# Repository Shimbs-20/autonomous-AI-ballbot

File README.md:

# 🤖 Hazard Detection Ball Bot — Cairo University GP 2026

<div align="center">

**A self-balancing omnidirectional robot on a spherical wheel with real-time hazard detection, autonomous SLAM navigation, and a live web dashboard.**

*Cairo University · Faculty of Engineering · Mechatronics Graduation Project · Spring 2026*

</div>

---

## 📋 Table of Contents

- [Overview](#overview)
- [Demo](#demo)
- [Team](#team)
- [System Architecture](#system-architecture)
- [Hardware](#hardware)
- [Software Stack](#software-stack)
- [Repository Structure](#repository-structure)
- [Quick Start](#quick-start)
- [Control System](#control-system)
- [Navigation](#navigation)
- [Hazard Detection](#hazard-detection)
- [Web Dashboard](#web-dashboard)
- [Results](#results)
- [Bill of Materials](#bill-of-materials)
- [Acknowledgements](#acknowledgements)

---

## Overview

The Hazard Detection Ball Bot is an inverted-pendulum robot that balances on a single 350mm sphere driven by three omnidirectional wheels. It combines:

- **Real-time dynamic balancing** using a custom EKF (8-state) and LQI controller running at 200 Hz on STM32F411
- **Autonomous SLAM mapping** using a 360° LiDAR and slam_toolbox on Raspberry Pi 4
- **Hazard detection** using a custom-trained YOLOv8 NCNN model (fire, smoke, electrical hazard, person, obstacle) at 33+ FPS
- **Full ROS2 Navigation Stack** with MPPI holonomic controller for autonomous goal-seeking
- **Live web dashboard** accessible from any browser on the local network

The robot operates in four modes:
| Mode | Description |
|------|-------------|
| `0 STANDBY` | Motors off, safe state |
| `1 BALANCE` | Stationary self-balancing (LQI active) |
| `2 TELEOP` | Balance + velocity commands from Pi |
| `3 FLOOR DRIVE` | Direct omni-drive on casters (for SLAM mapping without balance risk) |

---

## Demo

> 📹 **[Demo Video — YouTube](#)** ← add link after recording

| SLAM Mapping | Hazard Detection | Dashboard |
|:---:|:---:|:---:|
|  |  |  |

---

## System Architecture

```
┌─────────────────────────────────────────────────────────────────────┐
│                        RASPBERRY PI 4B                              │
│                                                                     │
│  LD06 LiDAR ──→ /scan ──→ slam_toolbox ──→ /map                    │
│                              ↑                                      │
│  /odom ←── stm32_bridge ←── UART2 ←─────────────────────┐         │
│               │                                           │         │
│               └──→ twist_mux ──→ /cmd_vel ───────────────┘         │
│                      ↑              ↑                               │
│               PS4 joystick    Nav2 MPPI                             │
│                                                                     │
│  IMX219 ──→ /image_raw ──→ YOLOv8 NCNN ──→ /hazard_detections     │
│                                 └──→ /image_annotated               │
│                                                                     │
│  web_video_server (port 8080) + rosbridge (port 9090)               │
└──────────────────────────────┬──────────────────────────────────────┘
                               │ UART2 / 115200 baud
                               │ TX: 16-byte [AA][55][mode][vx][vy][yaw][XOR]
                               │ RX: 27-byte [BB][66][x][y][θ][vx][vy][yaw][XOR]
┌──────────────────────────────┴──────────────────────────────────────┐
│                    STM32F411 @ 96 MHz / FreeRTOS                    │
│                                                                     │
│  MPU6050 ──→ EKF (200 Hz, 8-state) ──→ LQI K[3×10]               │
│                        ↑                     ↓                      │
│  Encoders (TIM2/3/4) ──┘           convert_torque_to_speed          │
│                                             ↓                       │
│  TIM11 ISR (70021 Hz) ─── Bresenham ──→ 3× DM860H ──→ NEMA34      │
└─────────────────────────────────────────────────────────────────────┘
```

---

## Hardware

### Key Specifications

| Component | Specification |
|-----------|--------------|
| **Compute (embedded)** | STM32F411CEU6 @ 96 MHz, 128KB RAM |
| **Compute (high-level)** | Raspberry Pi 4B, 4GB RAM |
| **Motors** | 3× NEMA34 86BYGH127, 8.5 N·m holding torque |
| **Motor Drivers** | 3× DM860H, 48V / 7.2A, 16-microstep |
| **IMU** | MPU6050, ±16g / ±2000°/s, DLPF 44 Hz |
| **LiDAR** | LD06, 360°, 12m range, 230,400 baud |
| **Camera** | IMX219 (Pi Camera v2), 1080p, 30 FPS |
| **Ball** | 350mm diameter, rubber-tape coated, µ≈0.50 |
| **Battery** | 48V / 11Ah NMC (EV Raid) |
| **Total Height** | 925 mm |
| **Total Mass** | ~17 kg |

### Kinematic Geometry

```
Wheel placement:  γ₁=120°, γ₂=240°, γ₃=0° (equal spacing)
Zenith angle:     α = 45°
Ball radius:      Rk = 0.175 m
Wheel radius:     Rw = 0.0625 m
```

---

## Software Stack

```
Firmware (STM32):          ROS2 (Raspberry Pi):
  FreeRTOS                   ROS2 Humble / Jazzy
  STM32 HAL                  slam_toolbox (async SLAM)
  EKF (custom C)             Nav2 (MPPI Omni)
  LQI controller             AMCL localization
  USART2 DMA                 twist_mux
  Bresenham step engine      web_video_server
                             rosbridge_websocket
Vision:                    Dashboard:
  OpenCV                     HTML5 / JavaScript
  Ultralytics YOLOv8         ROSLIB.js
  NCNN inference             Web Video Server MJPEG
```

---

## Repository Structure

```
ballbot/
├── README.md
├── LICENSE
├── .gitignore
│
├── firmware/                   STM32CubeIDE project
│   ├── Core/
│   │   ├── Src/
│   │   │   ├── main.c          Main control loop (Modes 0-3)
│   │   │   ├── lqr.c           LQI controller + EKF interface
│   │   │   ├── Ekf.c           Extended Kalman Filter (8-state)
│   │   │   └── mpu6050.c       IMU driver
│   │   └── Inc/
│   │       ├── lqr.h
│   │       └── Ekf.h
│   └── README.md
│
├── ros2_ws/                    ROS2 workspace
│   └── src/
│       ├── ballbot_controller/ Bridge, teleop, mode control
│       ├── ballbot_mapping/    SLAM toolbox config + launch
│       ├── ballbot_navigation/ Nav2 params, behavior tree
│       ├── camera_pi/          Camera node + YOLOv8 detector
│       └── gp_description/     URDF + mesh files
│
├── matlab/                     Design and simulation
│   ├── system_model/           Nonlinear ball-bot dynamics
│   ├── lqi_design/             LQI gain matrix K[3×10] derivation
│   ├── ekf_design/             EKF Q/R tuning + verification
│   └── simulation/             Full closed-loop Simulink model
│
├── hardware/
│   ├── cad/                    SolidWorks assembly (.SLDASM, .STEP)
│   ├── pcb/                    Custom power board schematics
│   ├── BOM.md                  Complete bill of materials
│   └── README.md
│
└── dashboard/
    └── dashboard.html          Standalone web dashboard
```

---

## Quick Start

### Prerequisites

```bash
# On Raspberry Pi 4B — Bookworm 64-bit
sudo apt install -y ros-humble-desktop python3-colcon-common-extensions \
    ros-humble-slam-toolbox ros-humble-nav2-bringup \
    ros-humble-rosbridge-server ros-humble-web-video-server

pip install ultralytics opencv-python picamera2
```

### Build

```bash
cd ~/ros2_ws
colcon build --symlink-install
source install/setup.bash
```

### Run — Hardware bringup (Terminal 1)

```bash
# Testing without STM32
ros2 launch ballbot_controller pi_controller.launch.py

# Real robot — stationary balance
ros2 launch ballbot_controller pi_controller.launch.py \
    use_fake_odom:=false robot_mode:=1

# Real robot — SLAM mapping on floor (safest)
ros2 launch ballbot_controller pi_controller.launch.py \
    use_fake_odom:=false robot_mode:=3
```

### Run — SLAM mapping (Terminal 2)

```bash
ros2 launch ballbot_mapping slam.launch.py use_slam:=true

# Drive to map:
ros2 run teleop_twist_keyboard teleop_twist_keyboard

# Save when done:
ros2 run nav2_map_server map_saver_cli -f ~/maps/room
```

### Run — Autonomous navigation (Terminal 2)

```bash
ros2 launch ballbot_mapping slam.launch.py \
    use_slam:=false map_yaml:=~/maps/room.yaml

ros2 launch ballbot_navigation nav2.launch.py \
    use_slam:=false shelf_test:=false
# Then: RViz → 2D Pose Estimate → 2D Nav Goal
```

### Run — Camera + Hazard detection (Terminal 3)

```bash
ros2 launch camera_pi hazard.launch.py
# Dashboard: http://ballbot.local:8080
```

### Switch robot modes at runtime

```bash
ros2 topic pub --once /ballbot/mode std_msgs/msg/UInt8 '{data: 1}'  # BALANCE
ros2 topic pub --once /ballbot/mode std_msgs/msg/UInt8 '{data: 2}'  # TELEOP
ros2 topic pub --once /ballbot/mode std_msgs/msg/UInt8 '{data: 3}'  # FLOOR DRIVE
```

---

## Control System

### EKF — 8-State Observer

State vector: `[φ, θ, dφ, dθ, Vx, Vy, bias_x, bias_y]`

- **Sensor fusion**: MPU6050 gyro + accelerometer + 3 wheel encoders
- **Accelerometer spike rejection**: rejects readings outside [0.2g, 15g]
- **Motor-aware noise**: R_accel scales with motor speed (30→250)
- **Execution time**: ~0.4ms @96MHz (Joseph-form covariance update)

### LQI Controller — K[3×10]

```
Torque = −K × [φ, θ, ψ, Vx, Vy, dφ, dθ, ω_z, ∫Vx, ∫Vy]ᵀ
```

Gains tuned in MATLAB for: m=17kg, Rk=0.175m, Rw=0.0625m, α=45°, J_wheel=0.0032 kg·m²

### Inverse Kinematics (Mode 3 — Floor Drive)

Pseudo-inverse of forward kinematic matrix (verified: K·K⁺=I₂ₓ₂):

```
ω₁ = −1.617·vx − 0.933·vy + 1.980·ω_z
ω₂ = +1.617·vx − 0.933·vy + 1.980·ω_z
ω₃ = +0.000·vx + 1.867·vy + 1.980·ω_z
```

---

## Navigation

- **SLAM**: slam_toolbox async_online, 5cm/cell, Ceres solver
- **Localization**: AMCL with OmniMotionModel
- **Planner**: SmacPlanner2D (A*, holonomic — no heading constraint)
- **Controller**: MPPI, 300 trajectories, `motion_model: Omni`, vy_max=0.5 m/s
- **Behavior tree**: ClearCostmap → Spin → BackUp → Wait
- **Velocity arbitration**: twist_mux — PS4(100) > keyboard(50) > Nav2(10)

---

## Hazard Detection

| Class | mAP@0.5 | Triggers E-Stop |
|-------|---------|-----------------|
| 🔥 Fire | 94.2% | ✅ |
| 💨 Smoke | 91.8% | ✅ |
| ⚡ Electrical Hazard | 88.7% | ✅ |
| 👤 Person | 96.5% | ❌ |
| 🚧 Obstacle | 85.3% | ❌ |

- **Model**: YOLOv8n converted to NCNN for Pi 4 CPU inference
- **Input**: 416×416 letterbox (aspect-ratio preserving)
- **Output**: 640×480 annotated MJPEG to web dashboard
- **Throughput**: 33.4 FPS average on Raspberry Pi 4B

---

## Web Dashboard

Accessible at `http://ballbot.local:8080` or `http://<Pi-IP>:8080`

**Features:**
- Live MJPEG camera feed (annotated with bounding boxes)
- Real-time SLAM map rendering from `/map` OccupancyGrid
- LiDAR scan overlay on map
- Odometry trail
- Mode control buttons (0/1/2/3) via `/ballbot/mode`
- Hazard detection cards with proximity indicator
- CPU temperature gauge
- Emergency stop overlay

**Dependencies:** rosbridge_websocket (port 9090), web_video_server (port 8080)

---

## Results

| Metric | Value |
|--------|-------|
| Control loop frequency | 200 Hz |
| EKF execution time | ~0.4 ms |
| Stepper ISR frequency | 70,021 Hz |
| SLAM map resolution | 5 cm/cell |
| Nav2 goal success rate | 100% (lab trials) |
| Detection FPS | 33.4 FPS |
| Detection classes | 5 |
| Total system mass | 17 kg |
| Battery endurance | ~2 hours |

---

## Bill of Materials

See [`hardware/BOM.md`](hardware/BOM.md) for the complete list.

**Major components:**

| Item | Qty | Est. Cost |
|------|-----|-----------|
| STM32F411 Black Pill | 1 | $5 |
| Raspberry Pi 4B 4GB | 1 | $55 |
| NEMA34 stepper 86BYGH127 | 3 | $45 each |
| DM860H stepper driver | 3 | $30 each |
| MPU6050 IMU module | 1 | $3 |
| LD06 LiDAR | 1 | $90 |
| Pi Camera Module v2 (IMX219) | 1 | $25 |
| 48V 11Ah NMC battery pack | 1 | $120 |
| Omni roller ball 350mm | 1 | $80 |
| **Total (approx.)** | | **~$1,480** |

---

## Acknowledgements

This project was completed as the Graduation Project 2 (GP2) for the Mechatronics program at Cairo University Faculty of Engineering, Spring 2026.

We thank Dr. Hossam H. Ammar and Dr. Moataz El-Sisi for their guidance throughout the project.

**References:**
- Lauwers, T. B. et al., "A Dynamically Stable Single-Wheeled Mobile Robot with Inverse Mouse-Ball Drive" — ICRA 2006
- Geyer, H., "Ballbot: The Fast, Omnidirectional Balancing Mobile Robot" — CMU 2010
- Welch, G. and Bishop, G., "An Introduction to the Kalman Filter" — UNC 1995

---

<div align="center">
Cairo University · Faculty of Engineering · Spring 2026
</div>

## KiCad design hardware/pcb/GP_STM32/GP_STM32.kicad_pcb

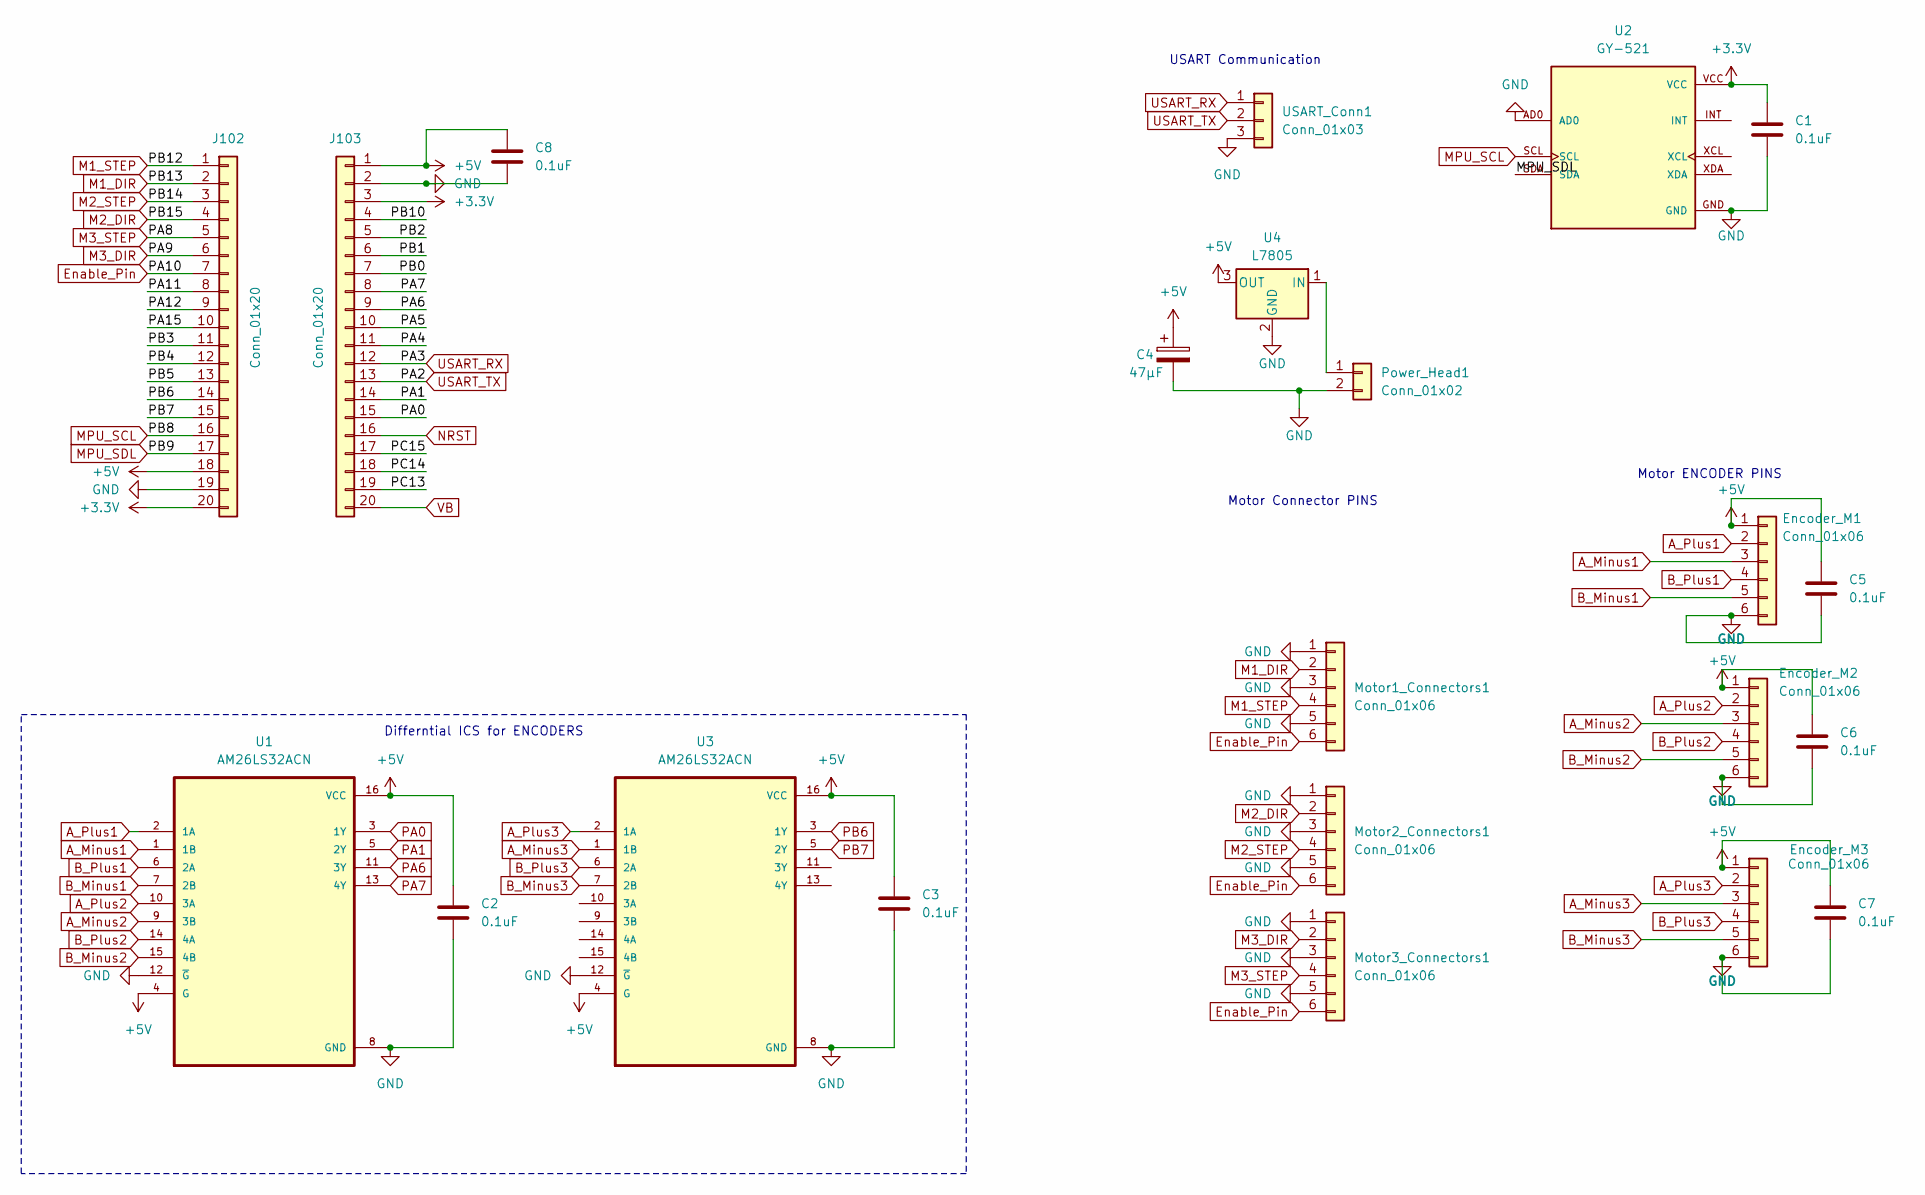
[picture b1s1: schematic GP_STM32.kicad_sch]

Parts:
C1, C2, C3, C5, C6, C7, C8: 0.1uF; C_Disc_D5.0mm_W2.5mm_P5.00mm
C4: 47µF; CP_Radial_D6.3mm_P2.50mm
Encoder_M1, Encoder_M2, Encoder_M3: Conn_01x06; JST_XH_B6B-XH-A_1x06_P2.50mm_Vertical
J102, J103: Conn_01x20; PinHeader_1x20_P2.54mm_Vertical
Motor1_Connectors1, Motor2_Connectors1, Motor3_Connectors1: Conn_01x06; JST_XH_B6B-XH-A_1x06_P2.50mm_Vertical
Power_Head1: Conn_01x02; TerminalBlock_MaiXu_MX126-5.0-02P_1x02_P5.00mm
U1, U3: AM26LS32ACN; DIP-16_W7.62mm
U2: GY-521; MODULE_GY-521; PARTREV NA
U4: L7805; TO-220-3_Vertical
USART_Conn1: Conn_01x03; JST_XH_B3B-XH-A_1x03_P2.50mm_Vertical

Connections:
+3.3V: C1.1, J102.20, J103.3, U2.VCC
+5V: C2.1, C3.1, C4.1, C5.1, C6.1, C7.1, C8.1, Encoder_M1.1, Encoder_M2.1, Encoder_M3.1, J102.18, J103.1, U1.4 (G), U1.16 (VCC), U3.4 (G), U3.16 (VCC), U4.3 (OUT)
/PA4: J103.11
/PA5: J103.10
/PA11: J102.8
/PA12: J102.9
/PA15: J102.10
/PB0: J103.7
/PB1: J103.6
/PB2: J103.5
/PB3: J102.11
/PB4: J102.12
/PB5: J102.13
/PB10: J103.4
/PC13: J103.19
/PC14: J103.18
/PC15: J103.17
A_Minus1: Encoder_M1.3, U1.1 (1B)
A_Minus2: Encoder_M2.3, U1.9 (3B)
A_Minus3: Encoder_M3.3, U3.1 (1B)
A_Plus1: Encoder_M1.2, U1.2 (1A)
A_Plus2: Encoder_M2.2, U1.10 (3A)
A_Plus3: Encoder_M3.2, U3.2 (1A)
B_Minus1: Encoder_M1.5, U1.7 (2B)
B_Minus2: Encoder_M2.5, U1.15 (4B)
B_Minus3: Encoder_M3.5, U3.7 (2B)
B_Plus1: Encoder_M1.4, U1.6 (2A)
B_Plus2: Encoder_M2.4, U1.14 (4A)
B_Plus3: Encoder_M3.4, U3.6 (2A)
Enable_Pin: J102.7, Motor1_Connectors1.6, Motor2_Connectors1.6, Motor3_Connectors1.6
GND: C1.2, C2.2, C3.2, C4.2, C5.2, C6.2, C7.2, C8.2, Encoder_M1.6, Encoder_M2.6, Encoder_M3.6, J102.19, J103.2, Motor1_Connectors1.1, Motor1_Connectors1.3, Motor1_Connectors1.5, Motor2_Connectors1.1, Motor2_Connectors1.3, Motor2_Connectors1.5, Motor3_Connectors1.1, Motor3_Connectors1.3, Motor3_Connectors1.5, Power_Head1.2, U1.8 (GND), U1.12 (~G), U2.AD0, U2.GND, U3.8 (GND), U3.12 (~G), U4.2 (GND), USART_Conn1.3
M1_DIR: J102.2, Motor1_Connectors1.2
M1_STEP: J102.1, Motor1_Connectors1.4
M2_DIR: J102.4, Motor2_Connectors1.2
M2_STEP: J102.3, Motor2_Connectors1.4
M3_DIR: J102.6, Motor3_Connectors1.2
M3_STEP: J102.5, Motor3_Connectors1.4
MPU_SCL: J102.16, U2.SCL
MPU_SDL: J102.17, U2.SDA
NRST: J103.16
unnamed: Power_Head1.1, U4.1 (IN)
PA0: J103.15, U1.3 (1Y)
PA1: J103.14, U1.5 (2Y)
PA6: J103.9, U1.11 (3Y)
PA7: J103.8, U1.13 (4Y)
PB6: J102.14, U3.3 (1Y)
PB7: J102.15, U3.5 (2Y)
USART_RX: J103.12, USART_Conn1.1
USART_TX: J103.13, USART_Conn1.2
VB: J103.20

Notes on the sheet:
Differntial ICS for ENCODERS
USART Communication
Motor Connector PINS
Motor ENCODER PINS

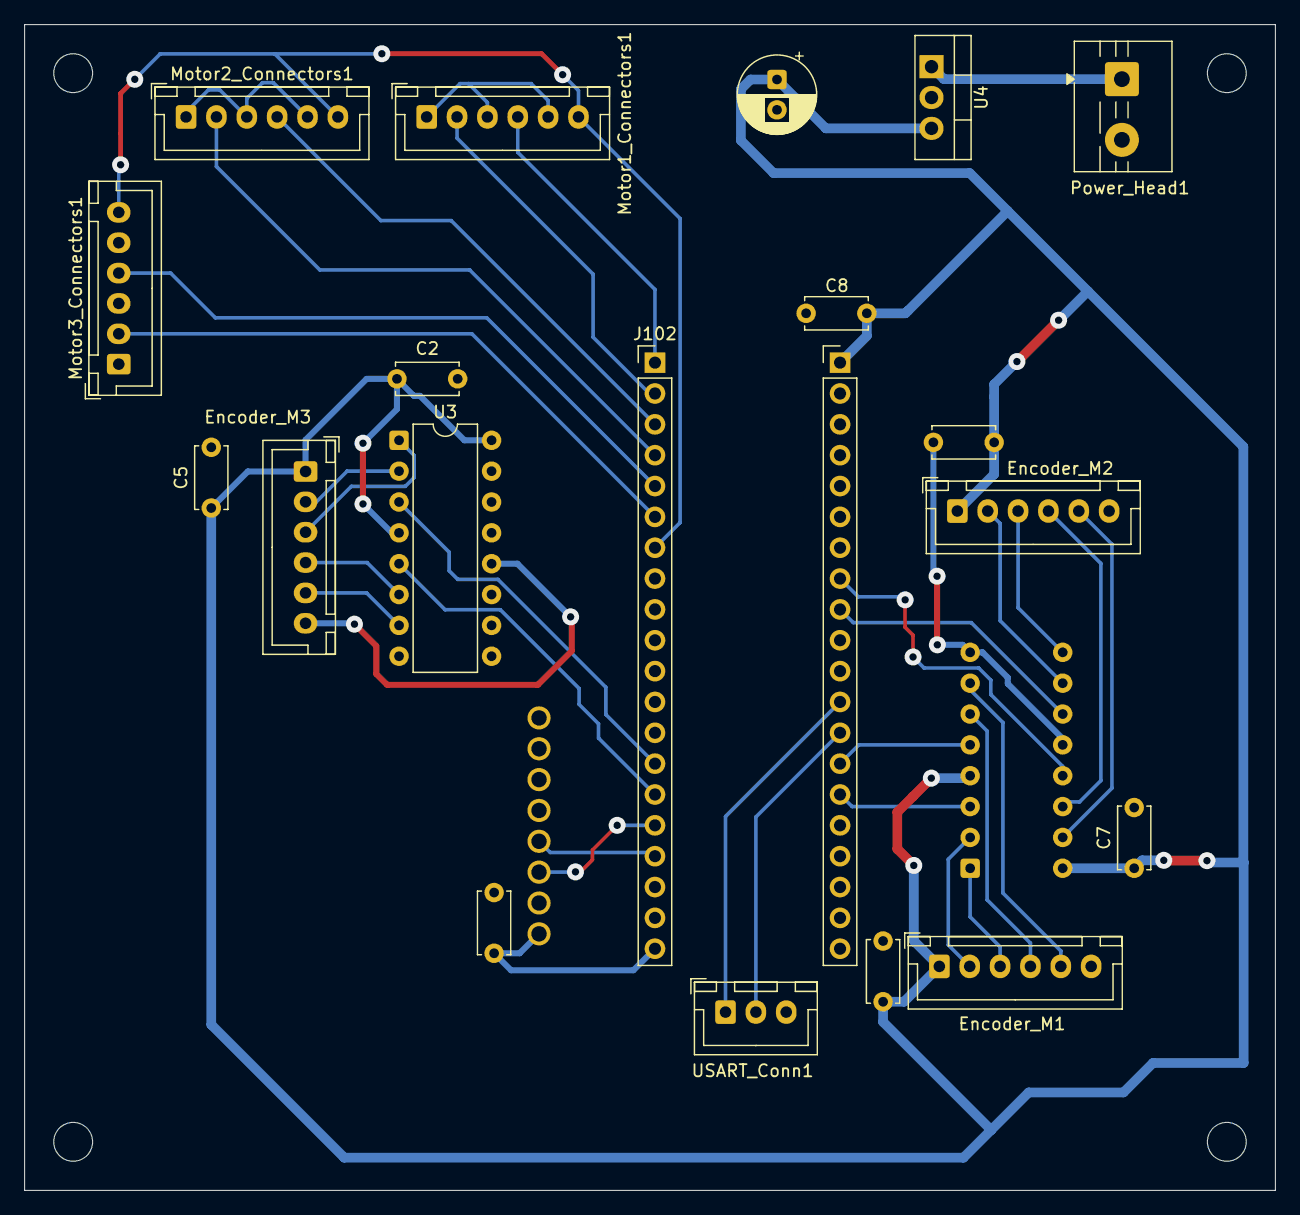
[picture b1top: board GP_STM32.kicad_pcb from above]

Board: 2 copper layers, 103.0 x 96.0 mm, 22 parts (1 on the bottom side), 33 nets.

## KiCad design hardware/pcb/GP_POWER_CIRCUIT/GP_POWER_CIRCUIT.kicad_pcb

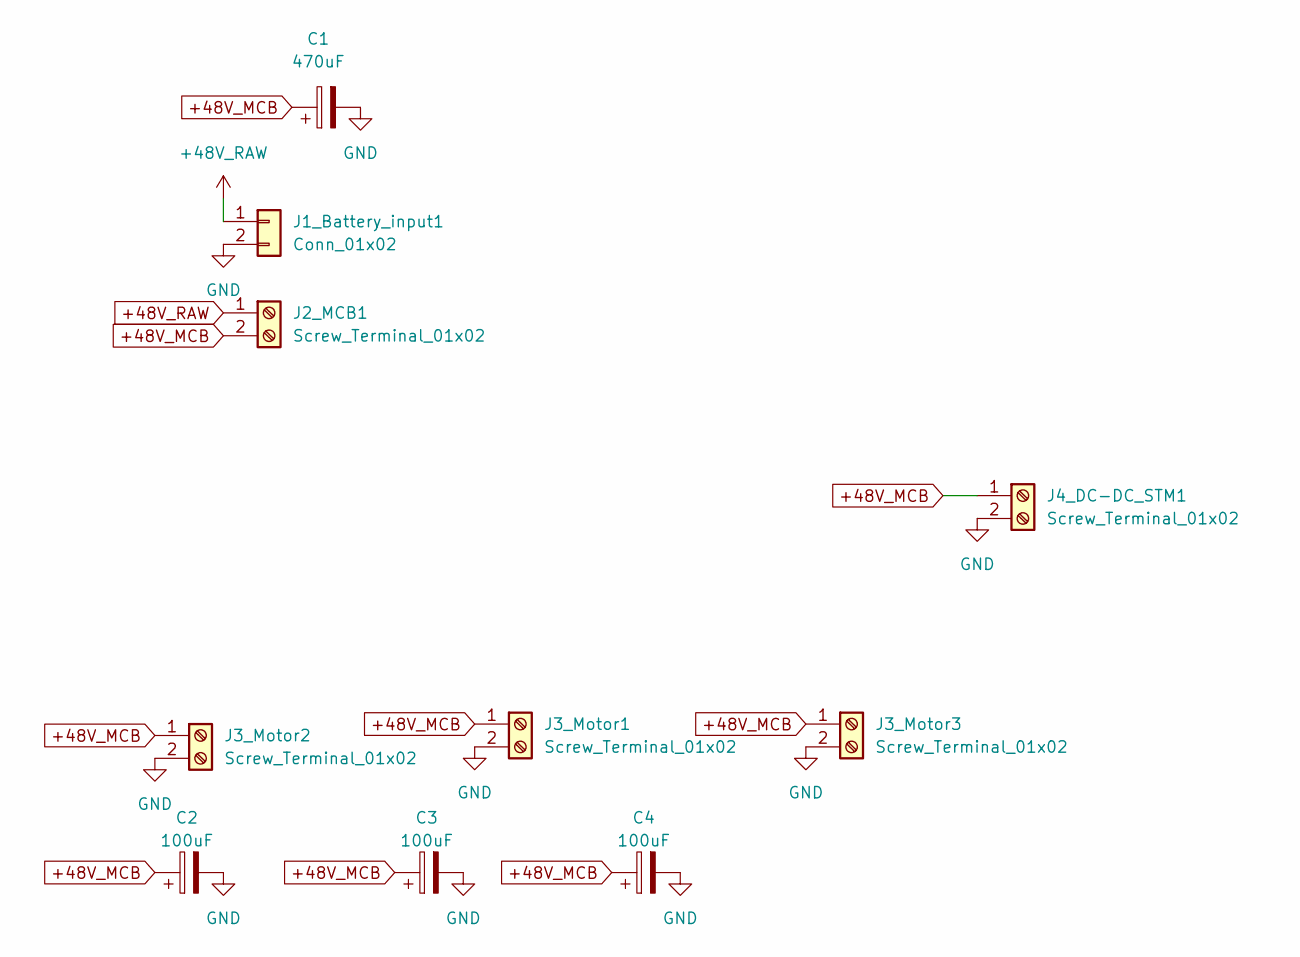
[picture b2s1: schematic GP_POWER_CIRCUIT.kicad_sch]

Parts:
C1: 470uF; CP_Radial_D10.0mm_P5.00mm
C2, C3, C4: 100uF; C_Disc_D5.0mm_W2.5mm_P2.50mm
J1_Battery_input1: Conn_01x02; AMASS_XT60-M_1x02_P7.20mm_Vertical
J2_MCB1, J3_Motor1, J3_Motor2, J3_Motor3, J4_DC-DC_STM1: Screw_Terminal_01x02; TerminalBlock_Phoenix_MKDS-1,5-2_1x02_P5.00mm_Horizontal

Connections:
+48V_MCB: C1.1, C2.1, C3.1, C4.1, J2_MCB1.2, J3_Motor1.1, J3_Motor2.1, J3_Motor3.1, J4_DC-DC_STM1.1
+48V_RAW: J1_Battery_input1.1, J2_MCB1.1
GND: C1.2, C2.2, C3.2, C4.2, J1_Battery_input1.2, J3_Motor1.2, J3_Motor2.2, J3_Motor3.2, J4_DC-DC_STM1.2

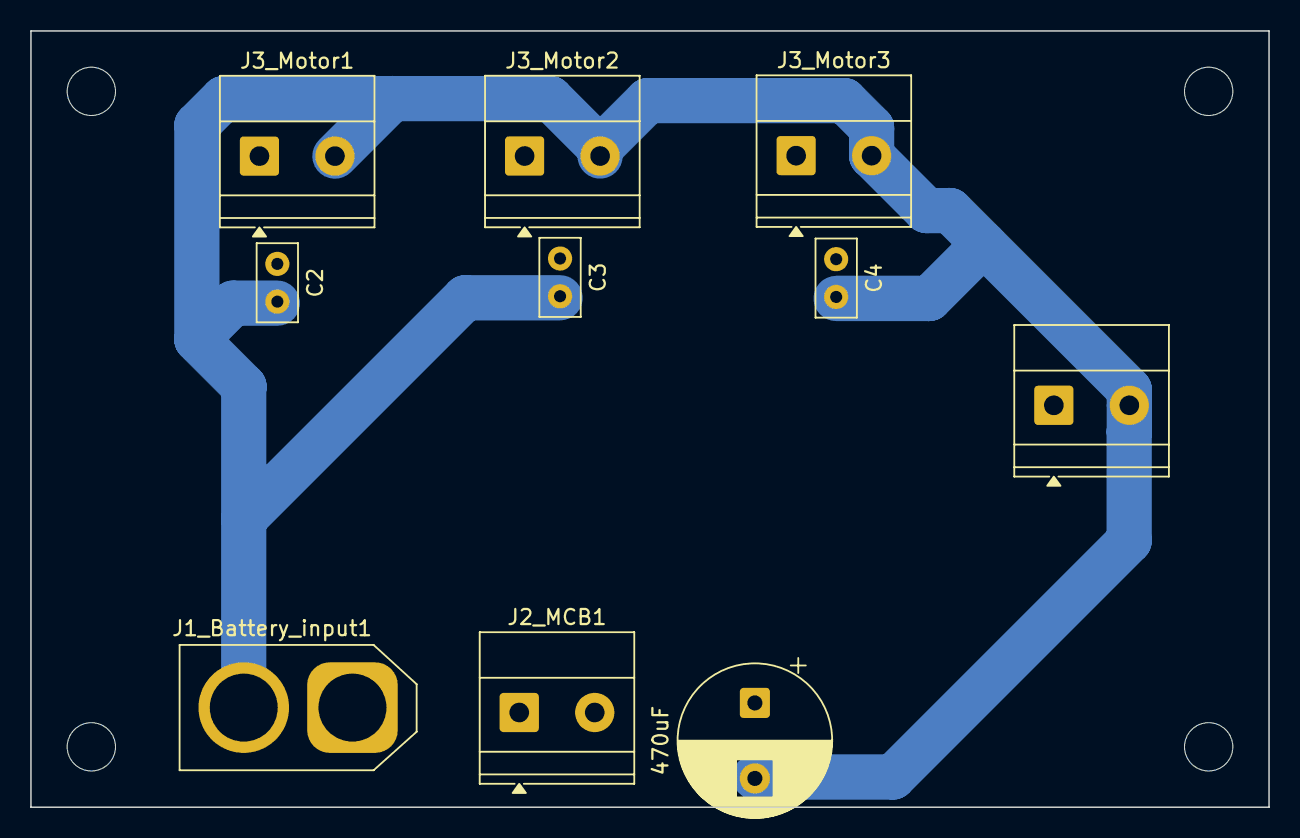
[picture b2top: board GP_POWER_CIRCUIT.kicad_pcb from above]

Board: 2 copper layers, 82.0 x 51.4 mm, 10 parts (0 on the bottom side), 3 nets.

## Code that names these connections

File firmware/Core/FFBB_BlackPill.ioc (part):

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Mcu.Name=STM32F411C(C-E)Ux
Mcu.Package=UFQFPN48
Mcu.UserName=STM32F411CEUx
PA0-WKUP.GPIOParameters=GPIO_Speed,GPIO_PuPd
PA0-WKUP.GPIO_PuPd=GPIO_PULLUP
PA0-WKUP.GPIO_Speed=GPIO_SPEED_FREQ_HIGH
PA0-WKUP.Signal=S_TIM2_CH1_ETR
PA1.GPIOParameters=GPIO_Speed,GPIO_PuPd
PA1.GPIO_PuPd=GPIO_PULLUP
PA1.GPIO_Speed=GPIO_SPEED_FREQ_HIGH
PA1.Signal=S_TIM2_CH2
PA10.GPIOParameters=GPIO_Label
PA10.GPIO_Label=ENABLE_PIN
PA10.Signal=GPIO_Output
PA11.Mode=Device_Only
PA11.Signal=USB_OTG_FS_DM
PA12.Mode=Device_Only
PA12.Signal=USB_OTG_FS_DP
PA13.Mode=Serial_Wire
PA13.Signal=SYS_JTMS-SWDIO
PA14.Mode=Serial_Wire
PA14.Signal=SYS_JTCK-SWCLK
PA15.GPIOParameters=GPIO_Label
PA15.GPIO_Label=M3_DIR1
PA15.Signal=GPIO_Output
PA2.Mode=Asynchronous
PA2.Signal=USART2_TX
PA3.Mode=Asynchronous
PA3.Signal=USART2_RX
PA6.GPIOParameters=GPIO_Speed,GPIO_PuPd
PA6.GPIO_PuPd=GPIO_PULLUP
PA6.GPIO_Speed=GPIO_SPEED_FREQ_HIGH
PA6.Signal=S_TIM3_CH1
PA7.GPIOParameters=GPIO_Speed,GPIO_PuPd
PA7.GPIO_PuPd=GPIO_PULLUP
PA7.GPIO_Speed=GPIO_SPEED_FREQ_HIGH
PA7.Signal=S_TIM3_CH2
PA8.GPIOParameters=GPIO_Label
PA8.GPIO_Label=M3_STEP
PA8.Signal=GPIO_Output
PA9.GPIOParameters=GPIO_Label
PA9.GPIO_Label=M3_DIR
PA9.Signal=GPIO_Output
PB1.GPIOParameters=GPIO_Label
PB1.GPIO_Label=ENAPLE_M2
PB1.Signal=GPIO_Output
PB12.GPIOParameters=GPIO_Label
PB12.GPIO_Label=M1_STEP
PB12.Signal=GPIO_Output
PB13.GPIOParameters=GPIO_Label
PB13.GPIO_Label=M1_DIR
PB13.Signal=GPIO_Output
PB14.GPIOParameters=GPIO_Label
PB14.GPIO_Label=M2_STEP
PB14.Signal=GPIO_Output
PB15.GPIOParameters=GPIO_Label
PB15.GPIO_Label=M2_DIR
PB15.Signal=GPIO_Output
PB6.GPIOParameters=GPIO_Speed,GPIO_PuPd
PB6.GPIO_PuPd=GPIO_PULLUP
PB6.GPIO_Speed=GPIO_SPEED_FREQ_HIGH
PB6.Signal=S_TIM4_CH1
PB7.GPIOParameters=GPIO_Speed,GPIO_PuPd
PB7.GPIO_PuPd=GPIO_PULLUP
PB7.GPIO_Speed=GPIO_SPEED_FREQ_HIGH
PB7.Signal=S_TIM4_CH2
PB8.GPIOParameters=GPIO_Pu
PB8.GPIO_Pu=GPIO_PULLUP
PB8.Mode=I2C
PB8.Signal=I2C1_SCL
PB9.GPIOParameters=GPIO_Pu
PB9.GPIO_Pu=GPIO_PULLUP
PB9.Mode=I2C
PB9.Signal=I2C1_SDA
PC13-ANTI_TAMP.GPIOParameters=GPIO_Label
PC13-ANTI_TAMP.GPIO_Label=Black_Pill_LED
PC13-ANTI_TAMP.Signal=GPIO_Output
PC14-OSC32_IN.GPIOParameters=GPIO_Label
PC14-OSC32_IN.GPIO_Label=ENAPLE_M3
PC14-OSC32_IN.Signal=GPIO_Output
PH0\ -\ OSC_IN.Mode=HSE-External-Oscillator
PH0\ -\ OSC_IN.Signal=RCC_OSC_IN
PH1\ -\ OSC_OUT.Mode=HSE-External-Oscillator
PH1\ -\ OSC_OUT.Signal=RCC_OSC_OUT
RCC.HSE_VALUE=25000000
RCC.SYSCLKFreq_VALUE=96000000
RCC.SYSCLKSource=RCC_SYSCLKSOURCE_PLLCLK
board=custom

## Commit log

2026-06-17 Initial commit — Cairo University Autonomous AI Ballbot GP 2026
2026-06-17 removed files
2026-06-17 Remove team information from README
    Removed team section and related details from README.
2026-06-17 Updated in some texts

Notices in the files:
README.md:
License: MIT
